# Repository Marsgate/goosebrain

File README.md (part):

# goosebrain rev 2: brain + smart pack, manual routing

This repo holds two boards that ship as one system:

- **The brain** (`kicad/thegoose.kicad_pro`): an RP2354A robot controller for six DC motors and six IO ports, with a USB-A host for a 2.4 GHz controller dongle. Its USB-C port is for programming only.
- **The smart pack** (`kicad-pack/goosepack.kicad_pro`): a small board that sits on the Ovonic 3S 450 mAh cells. It carries the charger, the protector, the 15 A fuse and its own USB-C charging port, and it plugs into the brain over an XT30 lead. Packs can be swapped, and spares can be sold.
- **The 2S smart pack** (`kicad-pack-2s/goosepack2s.kicad_pro`, started 2026-10-19): the same pack for 2-cell batteries. The charger is set for 2S by resistors, the protector is a HYCON HY2120-LB, and two HYCON HY2213 balancers replace the BQ7791501's balancing. See "The 2S pack board" below and PARTS.md. The brain runs from either pack.

The schematics are done. **The brain is placed on both sides and fully routed on 6 layers** (branch `double-sided`, 2026-10-20): 0 DRC errors, 0 unconnected items, ERC clean. See "The brain board" below and [ROUTING_LOG.md](ROUTING_LOG.md). The 3S pack board is placed and routed on 4 layers (2026-10-27, see "The pack board"); the 2S pack board is still unplaced and unrouted.

It was developed in a separate repo (goosebrain-manual), copied on 2026-10-19 from branch `rev2-rp2350` (commit `0ed7122` plus the uncommitted changes at the time) and split into brain + pack the same day. On 2026-10-20 that work, with its full history, was merged back into [Marsgate/goosebrain](https://github.com/Marsgate/goosebrain) `main`. The old SKiDL circuit generator (`circuit/`) was retired then: the KiCad schematics are the source of truth.

## The system

- **Charging:** plug the pack's USB-C into any 5 V USB charger. The pack is a plain 5 V sink (5.1 kΩ Rd on CC1/CC2, no PD), so VBUS stays at 5 V.
  - The BQ25798 runs standalone, from its power-on defaults: 3S (12.6 V), termination on, 12 h safety timer, JEITA temperature window, ADC off. No firmware can change it.
  - The ILIM_HIZ divider (39k / 24k from REGN) caps the input at about **1.04 A** (0.94–1.13 A over REGN tolerance). That gives about 0.44 A into the cells at 3.5 V/cell (1C) and 0.38 A at 4.1 V/cell, so a full charge takes about **1.2–1.3 h**.
  - A PC's USB-A port (BC1.2 SDP) is limited to 0.5 A, so charging from one takes about twice as long.
  - **The green LED on the pack** is lit while charging, off when full, and blinks on a fault.
  - **There is no cell thermistor** (removed 2026-10-26: the cells sit on the board's top side, with the parts, so no NTC can press on them). R79, a fixed 10 kΩ in TH2's old place, holds the charger's TS pin at the 25 °C point, so it always charges at the full rate and JEITA never kicks in. The protector's NTC (TH1, by the FETs) still trips on the board's temperature.
- **Protection:** BQ7791501 with low-side FETs and a 2 mΩ shunt. OV 4.25 V, UV 2.8 V per cell, OCD1 17.5 A (14 A worst case), OCD2 30 A, SCD 60 A, OCC 10 A, plus the 15 A fast fuse.
- **Clearing a trip:** an over-current trip clears when the load goes away. **Unplug the pack, or switch the brain off and on.** R94 (100 kΩ, PACK− to cell −) lets the protector see the load removed even with the charger's 17 µA standby draw on the pack.
- **The brain** takes the pack's XT30U-F lead on J3, a horizontal XT30PW-M whose mouth faces out through the bottom wall (pin 1 GND = PACK−, pin 2 PACK+). The power switch drives Q1. With the switch off, nothing on the brain loads the pack.
- **Programming:** the brain's USB-C powers the MCU through U8 alone, so you can flash it with no pack or with the switch off.

## Firmware changes

- **`code/` is the old firmware.** It's the ESP32 program (Bluepad32, ESP32Servo, DRV8848 pins) from before rev 2 and doesn't run on the RP2354A. Rev 2 needs a new firmware built around the pin map below and a USB host stack for the dongle (Pico-PIO-USB).
- **Core supply:** DVDD comes from an external 1.1 V LDO (U12), not the RP2354's own regulator (RP2350 datasheet §6.3.7). Early in boot, set the VREG register's HIZ bit to shut the on-chip regulator down (it starts anyway and draws about 400 µA until then). Never put it in low-power mode, which connects it straight to DVDD. The core voltage is fixed at 1.1 V, so don't raise it in software (`vreg_set_voltage`) or overclock past the default 150 MHz.
- **GPIO map (double-sided board, 2026-10-20):** the pins were reshuffled so each signal leaves U10 on the side facing where it goes. The MCU sheet's GPIO MAP note has the full list:
  - Motors (IN1/IN2, one PWM slice each): M1 GPIO26/27 (slice 5), M2 GPIO22/23 (slice 3), M3 GPIO20/21 (slice 2), M4 GPIO16/17 (slice 0), M5 GPIO12/13 (slice 6), M6 GPIO14/15 (slice 7).
  - LED stick data: GPIO29.
  - USB-A host: GPIO25 = D+, GPIO24 = D−. D− is the lower pin, so configure Pico-PIO-USB with `pin_dp = 25` and `pinout = PIO_USB_PINOUT_DMDP`.
  - Battery sense: GPIO28 (ADC2), unchanged.
- **Spare GPIOs:** GPIO4–7, GPIO10, GPIO11, GPIO18 and GPIO19 are no-connects.
- **IO ports:** IO1–IO6 are GPIO0, 1, 2, 3, 8 and 9. All six are 5 V tolerant, because none is on an ADC pin (GPIO26–29). IO4–IO6 can run servos from hardware PWM (slices 1B, 4A and 4B; IO5 and IO6 share slice 4, so they share a frequency), and no motor uses slice 1 or 4. IO1 and IO2 share slice 0 with M4, and IO3 shares slice 1 with IO4, so drive their servos from PIO.
- **No I2C charger:** drop the charger driver. The battery voltage now comes only from the GPIO28 divider (VSYS / 4.7, so 12.6 V reads 2.68 V). It reads 0 with the switch off.
- **The pack cuts off in hardware:** the 3S pack at 2.8 V per cell (8.4 V), the 2S pack at 2.8 V per cell (5.6 V; the HY2120 turns back on at 3.0 V per cell). Warn the user well above that, at about 3.3 V per cell.
- **Work out the cell count at power-on** from the GPIO28 reading: above about 8.6 V it's a 3S pack, otherwise 2S. The only pack this reads wrong is a nearly flat 3S one, and the cutoff is in hardware, so the cost is only a wrong warning level.
- **Motor speed:** the motors run about 40 % slower on a 2S pack. To make the robot behave the same on either pack, cap the 3S PWM to match.
- **Motors:** six DRV8251As, one per motor, on the GPIO pairs above (IN1 = GPIOn_MxA, IN2 = GPIOn_MxB). M2, M4 and M6 stay wired reversed. There is no DRV_SLEEP or DRV_FAULT: a driver sleeps when both inputs stay low for about 1 ms. Each driver limits itself at about 1.36 A (shared VREF 2.53 V, 1.2 kΩ on IPROPI, so 1.34 A). They run from 4.5 V, so a 2S pack works.
- **USB-A:** the port is always powered through a 0.5 A PTC. There is no USBA_VBUS_EN. R109/R114 (15 kΩ) are the host pull-downs on D+/D−, so Pico-PIO-USB doesn't need the GPIO pull-downs on GPIO24/25.
- **Start the USB host only when VSYS is present** (GPIO28 reads a pack). U11's VP is on VCC, which is 0 V on USB-C power alone; driving GPIO24/25 high then back-powers VCC (the dongle, J5's servos, the LED stick) at about 2.5 V through R48/R49 and U11's diodes.
- **Motor PWM:** a DRV8251A sleeps after 0.8–1.5 ms with both inputs low and takes 250 µs to wake, so use drive/brake (slow-decay) PWM, or coast PWM above a few kHz, so the off time never reaches that.
- **Entering BOOTSEL:** there's no RUN button, and with the pack on, +3V3 stays up through D3, so unplugging USB-C doesn't reset the chip. Switch off, hold BOOT (SW2) and plug in USB-C; or hold BOOT and short TP3 (RUN) to TP4 (GND); or reboot into BOOTSEL from firmware with picotool.
- **RP2350 erratum E9:** it affects only the A2 stepping, and R109/R114 (15 kΩ) are above its 8.2 kΩ limit. Read the stepping of the first boards (`picotool info`); on A2, a USB-A unplug may not be detected.

## Bring-up tests

1. **Pack charge current:** with a USB-C charger, measure the cell current at about 3.5 V/cell (expect about 0.42–0.44 A) and at 4.1 V/cell (about 0.36–0.38 A). Also try a C-to-C cable from a PD-only charger: the datasheet doesn't say what the BQ25798's D+/D− detection reports for a source with open D+/D−. If it reports SDP, charging is limited to 0.5 A in.
2. **Trip recovery:** short the pack output through a 10 A-rated load to trip OCD, then check that unplugging the pack clears it. Trip it again with the brain connected and check that the brain's power switch clears it.
3. **TS:** with USB-C in, check that TS (U7 pin 16) sits at about 59 % of REGN, inside the 10–45 °C band, and that charging runs at the full rate.
4. **Motors:** stall one motor and check the current chops at about 1.36 A.
5. **2S pack:** check that the charge stops at 8.4 V, measure the charge current (about 0.42 A at 3.5 V/cell), and check that each HY2213 bleeds about 89 mA once its cell passes 4.20 V. Trip the HY2120 with a load: over-current near 18–20 A, depending on how hot Q2/Q3 are. Then check that unplugging clears it.
6. **Brain on 2S:** at 5.6 V in (the 2S cutoff), check that Q1 is fully on (about −5 V gate drive), that VCC holds 4.96 V with the servos loaded, and that the soft start still takes about 70 µs with C71 at 10 nF.
7. **Core supply (+1V1):** measure +1V1 at C86 at idle, then with the CPU at its highest clock and the USB host running. It should stay at 1.1 V (U12's tolerance is ±1.4 %). Check that the firmware sets the VREG register's HIZ bit after boot: +3V3 current drops by about 0.4 mA when it does.
8. **Buck load step:** step the VCC load (servos) and watch VCC. If it rings, change C16 to 2.7 nF and add 39 pF from COMP (U4 pin 6) to GND, as DS41979 Table 1 does (there's no pad for it, so tack it onto C16's GND end). With L1 at 2.2 µH the ripple at 12.6 V in is about 2.7 A p-p, so expect about 4.5 A of usable output, not 5 A.
9. **Q1 turn-off:** switch off with a motor stalled and scope Q1's gate and VSYS. R40 (47k) with C71 + C72 takes about 5 ms to turn it off, so it passes through its linear region while the motors draw current.
10. **Shared motor VREF:** during test 4, also stall several motors at once and check that MOT_VREF stays at 2.53 V.

## Opening it

Open `kicad/thegoose.kicad_pro` or `kicad-pack/goosepack.kicad_pro` in KiCad 10. Both projects share the libraries in `kicad/`:

- `hexy.pretty`: the custom footprints.
- `hexyhustle.kicad_sym`: the custom symbols.
- `3dmodels`: the custom 3D models.

The pack's library tables point at `${KIPRJMOD}/../kicad/`.

## The brain board

- **Board:** 68.2 × 32 mm with 1 mm corner radii, **6 layers**, 1.6 mm thick, no mounting holes, **parts on both sides**.
  - It was 73.5 × 43.1 mm (3,169 mm²) before the double-sided build. Now it's 2,182 mm²: 31 % smaller, 5.3 mm shorter and 11.1 mm narrower.
  - It was 88.5 × 47 mm until 2026-10-19.
- **Parts:** the part numbers and the reasons behind them are in [PARTS.md](PARTS.md).
- **How it was built:** the placement, the routing passes, the 4-to-6-layer decision and the trade-offs are in [ROUTING_LOG.md](ROUTING_LOG.md). The copper is generated by scripts:
  - `tools/place_double.py` places every part.
  - `python3 tools/route_all.py` rebuilds all the copper from that placement in about 10 minutes: the scripted critical routing (`tools/route_recipe.py`), a small grid router for the rest (`tools/grid_router.py`), GND channels and stitching, and the silkscreen.
  - Hand edits to tracks are lost on the next rebuild, so change the scripts instead.

### Stackup: JLC06161H-3313

| Layer | Use | Thickness |
|---|---|---|
| F.Cu | parts, USB pairs, short signals, GND pour | 35 µm (1 oz) |
| prepreg 3313 | εr 4.1 | 0.0994 mm |
| In1.Cu | **solid GND** | 15 µm |
| core | | 0.55 mm |
| In2.Cu | signals, GND fill | 15 µm |
| prepreg 2116 | | 0.1088 mm |
| In3.Cu | GND with the VSYS, VCC and +3V3 areas; GND channels under every In2 signal | 15 µm |
| core | | 0.55 mm |
| In4.Cu | **solid GND** | 15 µm |
| prepreg 3313 | εr 4.1 | 0.0994 mm |
| B.Cu | back-side parts, signals, GND pour | 35 µm (1 oz) |

JLC quotes 1.54 mm finished.

The 4-layer stack (JLC04161H-7628) was tried first. It still left 27–60 connections unrouted after three placement passes, scripted critical routing and 30-minute Freerouting runs, and B.Cu signals would have crossed In2's power areas. Filled vias in pads are free on 6 layers. Impedance control was too when the move was made, but it cost $33.08 in the quote of 2026-10-20 (see "Ordering boards").

### What's on the board now

- **Top wall, left to right:** J1 (USB-C), J12 (LED stick, vertical PH) and J4 (USB-A). J1's and J4's plug centres are 19.5 mm apart, so an 8BitDo dongle (24 mm wide) fits next to a USB-C plug.
- **Left wall:** J5 (the 3 × 6 right-angle IO header) at the top, then M5 and M6.
- **Right wall:** M1–M4.
- **Bottom wall:** J3 (horizontal XT30) with its mouth out through the wall, SW1's lever, and SW2 (BOOT) in the bottom-right corner.
- **Front:**
  - U10 (RP2354A, at 0°) under J1, with Y1 next to it.
  - U10's core supply north-east of it: an external 1.1 V LDO (U12, TLV74311) as in the RP2350 datasheet's Fig. 24, with C86 (output) and C87 (input) beside it, so the on-chip switching regulator and its inductor aren't used. C85 (VREG_VIN) sits right off pins 47–49; VREG_FB goes to a GND via inside the pin ring and VREG_LX is open. C52, the second 4.7 µF, is on the back at DVDD pin 23.
  - The buck (U4, L1, C73/C74, C14) below U10.
  - U3/U17 beside M5/M6, and U1/U15/U2/U16 beside M1–M4.
  - Q1 east of J3.
- **Back** (all assembled by JLC except D4, U14 and F2), each part under or next to what it serves:
  - U10's decoupling, each cap on its supply via, and C52 (the second +1V1 4.7 µF) at DVDD pin 23
  - U6 (USB-C ESD) and R99/R100 under J1
  - U11, R109/R114, F2 and C59 under J4
  - U14 and C69 under J12
  - the 3.3 V LDO cluster (U8, U9, D2, C37–C40) under J3
  - the buck's output caps and feedback parts under L1
  - R55–R60 beside J5
  - the drivers' VM caps and IPROPI resistors
  - D4 and the Q1 gate network
  - TP1–TP4
  - The tallest back parts are the 1206 caps C5/C8/C12, at 1.6 mm.
- **Fiducials:** FID1–FID3 on the front and FID4–FID6 on the back. The goose logo is on the back silkscreen, wherever tools/silk.py finds room.
- **Routing:** complete.
  - `kicad-cli pcb drc --schematic-parity --severity-error` with zones refilled: 0 errors, 0 unconnected, 0 parity issues.
  - ERC: 0 violations.
  - The only DRC warnings are 9 footprints that differ from their library copies (M1–M6, J3, J4 and the logo). Their silk was trimmed at the outline, and the logo was scaled to fit.
  - 27 references are hidden: FID1–6, the caps under U10 (C52 among them), C85 by the core supply pins and a few others with no clear 0.8 mm spot. They're still on the fab layers.
- **Vias:** 0.45/0.3 mm for signals (168) and 0.6/0.3 mm for power (51), so the smallest hole on the board is 0.3 mm (the drivers' thermal vias are 0.33 mm). The signal vias were 0.45/0.25 mm until 2026-10-20; at 0.3 mm the order avoids JLC's small-via surcharge, and the annular ring is 0.075 mm. Several sit in pads, so order filled and capped vias (POFV), which are free on 6 layers.
- **"USB fan-out" rule areas:** they only exempt the short fan-out segments where a pair has to split from the diff-pair gap check.
- **"VREG corner" rule area:** over pins 47–50 and C85. The VREG_PGND, VREG_VIN and VREG_FB stubs are only as wide as the 0.2 mm pads, so inside it 0.15 mm spacing applies and the GND stubs are exempt from the 0.4 mm GND width.

## Routing rules

The net classes are set in the project file, and the custom DRC rules are in `kicad/thegoose.kicad_dru`.

| Class | Nets | Track | Clearance | Via (dia / drill) |
|---|---|---|---|---|
| Default | signals | 0.15 mm | 0.15 mm | 0.45 / 0.3 mm |
| Pack | PACK+, VSYS | 1.0 mm min | 0.2 mm | 0.8 / 0.4 mm |
| 5V | VCC, USB-A VBUS | 0.5 mm min | 0.2 mm | 0.6 / 0.3 mm |
| GND | GND | 0.4 mm min | 0.2 mm | 0.6 / 0.3 mm |
| Motor | U*_OUT1/2 | 0.4 mm min | 0.2 mm | 0.6 / 0.3 mm |
| Rail | +3V3, +1V1, VBUS | 0.2 mm | 0.2 mm | 0.45 / 0.3 mm |
| USB | USB pairs | 0.124 mm, 0.127 mm gap | 0.12 mm (0.2 mm to other nets) | 0.45 / 0.3 mm |

- **USB pairs:**
  - Route them as differential pairs: **0.124 mm tracks with a 0.127 mm gap**.
  - JLC's impedance calculator gives 90 Ω for that on F.Cu over In1 on JLC06161H-3313 (checked 2026-10-20). **Order with the stackup specified (JLC06161H-3313), not impedance control:** the stackup alone fixes the dielectric this geometry was sized for. Impedance control costs $33.08 on this order and needs an impedance spec sheet in the Gerber zip, and USB here runs at full speed (12 Mbit/s), where the pair's impedance barely matters.
  - The pairs run on F.Cu over solid In1, except J1's flipped contacts, which join on the back over solid In4.
- **Power widths:** the minimums in the table are DRC rules. Pours on those nets don't have to meet them.
- **Pack path:** PACK+ from J3 through Q1 to VSYS carries all the motor current, with stall peaks of several amps. It runs in pours on F.Cu and B.Cu and in the In3 VSYS area, with several vias at every layer change.
- **Switch node:** signals keep 0.2 mm from the buck switch node (U4 SW).
- **In2 signals** reference In3. `tools/plane_channels.py` cuts a GND channel (track + 0.5 mm each side) out of the In3 power areas under every In2 signal.
- **Board edge:** copper keeps 0.3 mm from the edge, JLC's limit for routed edges.

## The pack board

`kicad-pack/goosepack.kicad_pcb` is **placed and routed** (2026-10-27, charger reworked the same day): **50 × 23 mm**, the smallest board with every part on the top side (so JLC's Economic PCBA, top side only, still works) and every capacitor and resistor within 9 mm of the pin it serves (the TS, ILIM_HIZ and PROG dividers, which only set DC levels, and C34 sit further out). The parts also pack onto 45.5 × 20.5 mm, but only with the charger's last passives 13–22 mm from their pins, and that board didn't route. It uses the 4-layer JLC04161H-7628 stackup (the brain moved to 6 layers). DRC with zones refilled: 0 errors, 0 unconnected items, two warnings (J11's silk was trimmed at the board edge and U7's pin 1 mark nudged off C22, so neither matches its library footprint); schematic parity and ERC are clean. The housing is designed around this outline.

`tools/place_pack.py compact` rebuilds the placement (run with KiCad's Python; `--size` and `--reach` try other sizes and reach limits, `--led=stat` puts LED1 by U7 instead of the edge). Then `tools/route_pack.py setup`, `route` and `finish` rebuild the copper, and `tools/silk.py pack` places the references and the polarity labels (see each docstring). Routing takes about 10 minutes; every step takes `--pcb=FILE` to work on a copy, and `route --order=NET,...` tries another route order. Its other layouts (`vertical`, `rightangle`, `ontop`) were the earlier options for a board sized to the Ovonic pack; renders of all of them are in `renders/pack/`.

The whole process, from placement to the JLC order, with what went wrong along the way, is in [docs/3s-pack-process.md](docs/3s-pack-process.md). Follow it for the 2S pack.

- **Top:** power row along the bottom edge (J3 pads, F1 over R66, Q2/Q3 back to back, J2 pads), J11 and U13 above it, the charger and J1 at the east end, LED1 on the east edge above J1. J1's face sticks out about 1.4 mm past the east edge.
- **The charger's power stage** follows TI's BQ25798 layout example (SLUSDV2C §8.4.2): U7's power pins face west into L2, the SYS caps (C32, C27–C30) sit in a row north of L2 and the PMID caps (C26, C24, C25) in a row south of it, each row on an F.Cu pour from its pin with its 100 nF cap nearest, and PGND runs out between L2's pads to five vias under L2's body. The boot caps are 0402: C18 under L2 with its SW1 pad on the SW1 pour (BTST1 about 6.4 mm, partly on B.Cu), C19 over pin 19 (BTST2 1.5 mm; SW2 back by a via and about 7 mm of 0.4 mm In2). The REGN, VBUS and BAT caps sit at their pins.
- **Polarity:** B−/B+ by J3's pads (the cells), P−/P+ by J2's (the output; the square pads are negative), and B0–B3 under J11's pins.
- **Heights above the board:** J11 7.0 mm (about 12 mm with the balance plug in), J1 3.3 mm, L2 3.0 mm, F1 2.7 mm, D1 2.4 mm, the rest under 1.8 mm.
- **Back:** no parts, only the clipped leads of J2, J3 and J11 (keep them to 1.5 mm).
- **Pigtails:** J3 takes a 16 AWG lead ending in an XT30U-M that the pack's own XT30U-F plugs into, so the cell leads stay uncut. J2 takes the 16 AWG output lead with the XT30U-F that mates the brain's J3. Both use KiCad's `SolderWire-1.5sqmm_1x02_P6mm` pads. J11 stays a B4B-XH-A header: JST XH has no wire-to-wire male, so the balance lead can't become a pigtail.
- There are no mounting holes: the housing holds the board by its edges.
- The housing shows LED1 and the USB-C opening.
- R66 is a TA-I RLP25 2 mΩ 2512 metal shunt. It uses KiCad's generic 2512 land pattern for now: check TA-I's recommended pads before ordering.

Routing:

- **Layers:** F.Cu carries the parts, signals and the pack-path pours (J3 → F1 → PACK+, BAT_N → R66 → Q2 → Q3 → PACK- → J2). In1 is ground, split between BAT_N (the cells' negative, under the protector) and PACK- (the charger's and the brain's ground). In2 carries PACK+ in a band from F1 to J2 and is otherwise a signal layer. B.Cu carries signals. F.Cu, In2 and B.Cu are filled with the same ground split, stitched to In1 every 2.5 mm where both fills reach.
- **Widths:** the pack path and the charger's power stage are pours. Power and plane-net tracks are 0.4 mm. The charger's routed power nets (VBUS, PMID, SYS) are 0.3 mm, since the BQ25798's 0.2 mm pads at 0.4–0.46 mm pitch take nothing wider at 0.2 mm clearance; `finish` widens them to 0.4 mm wherever DRC still passes (VBUS and PACK+ to 0.6 or 0.5 mm on In2 first). VBUS still has about 12 mm of 0.3 mm on In2, which carries only C21's and D1's branches, not the input current. Signals are 0.15 mm.
- **Vias:** 0.45/0.3 mm for signals (as on the brain), 0.5/0.3 or 0.6/0.3 mm for the power classes (the router picks by net class), none within 0.2 mm of an SMD pad. The vias under U7's body (no exposed pad) are its east-side and corner escapes: SDA, SCL, SDRV, the east ground pins; VBUS's east pins join pins 2 and 3 by an F.Cu strip under the body instead.
- **Current sense:** Kelvin lines on B.Cu from vias at the inner edges of R66's pads to R68 and R69 (the SRP/SRN filter, with C68 across U13's pins). Rule areas keep the fills off the BAT_N line and its vias, so it meets BAT_N only at R66's pad.
- **Router:** `tools/grid_router.py --board=pack`, the brain's router. Freerouting 2.1 stalled at 25–40 unrouted connections and ignores its pass limits. `route_pack.py setup` lays the connections that no route order could fit around U7 (escape vias for its crowded corners and J1's CC2 and north VBUS pads, C18's and C19's boot loops, a stub out of C36's SDRV pad), and keeps ILIM_HIZ 1 mm off SW2's In2 run with a router-only keepout; `route` then routes STAT, CHG_SYS, BTST1 and PROG first and the rest in the router's own order. `tools/route_loop.py` wraps the router in a diagnose-and-retry loop for an LLM (or a person) to drive: each attempt routes a copy with `tools/route_llm.py` (grid_router plus a diagnosis of each failed pair; `tools/escape.py` adds pin escapes) and writes the failures, the nets in the way and a hint to a JSON report. That loop found the route orders above.

Open layout items (fresh-eyes reviews on 2026-10-27 scored the board 2.4, then 3.4 and 3.5 of 5 after the charger rework; the last found no blockers). Decided the same day: D1 is an SMBJ15A (24.4 V clamp, under the BQ25798's 30 V VBUS maximum; see PARTS.md) and the finish is lead-free HASL (ENIG would add $16.70 for 5 boards; OSP ages before the hand-soldered parts go on).

- **The boot loops** are the shortest this footprint allows with every part on top: TI's example runs SW1/SW2 through vias inside U7's pads, which single-sided assembly without via-in-pad can't do. BTST1 is about 6.4 mm with two vias, and C19's SW2 return about 7.7 mm through In2.
- **C36** (SDRV's 1 nF) sits about 9 mm from its pin's via; nothing closer is free, and SDRV is a static charge-pump output.
- **Q2 and Q3** only have the F.Cu drain pour for heat (about 1 W each at 15 A).
- **References:** 44 are hidden for lack of room (no reference may sit over another part); the fab layers keep them all.
- **R66** uses KiCad's generic 2512 land pattern: check TA-I's recommended pads (see above).

## The 2S pack board

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
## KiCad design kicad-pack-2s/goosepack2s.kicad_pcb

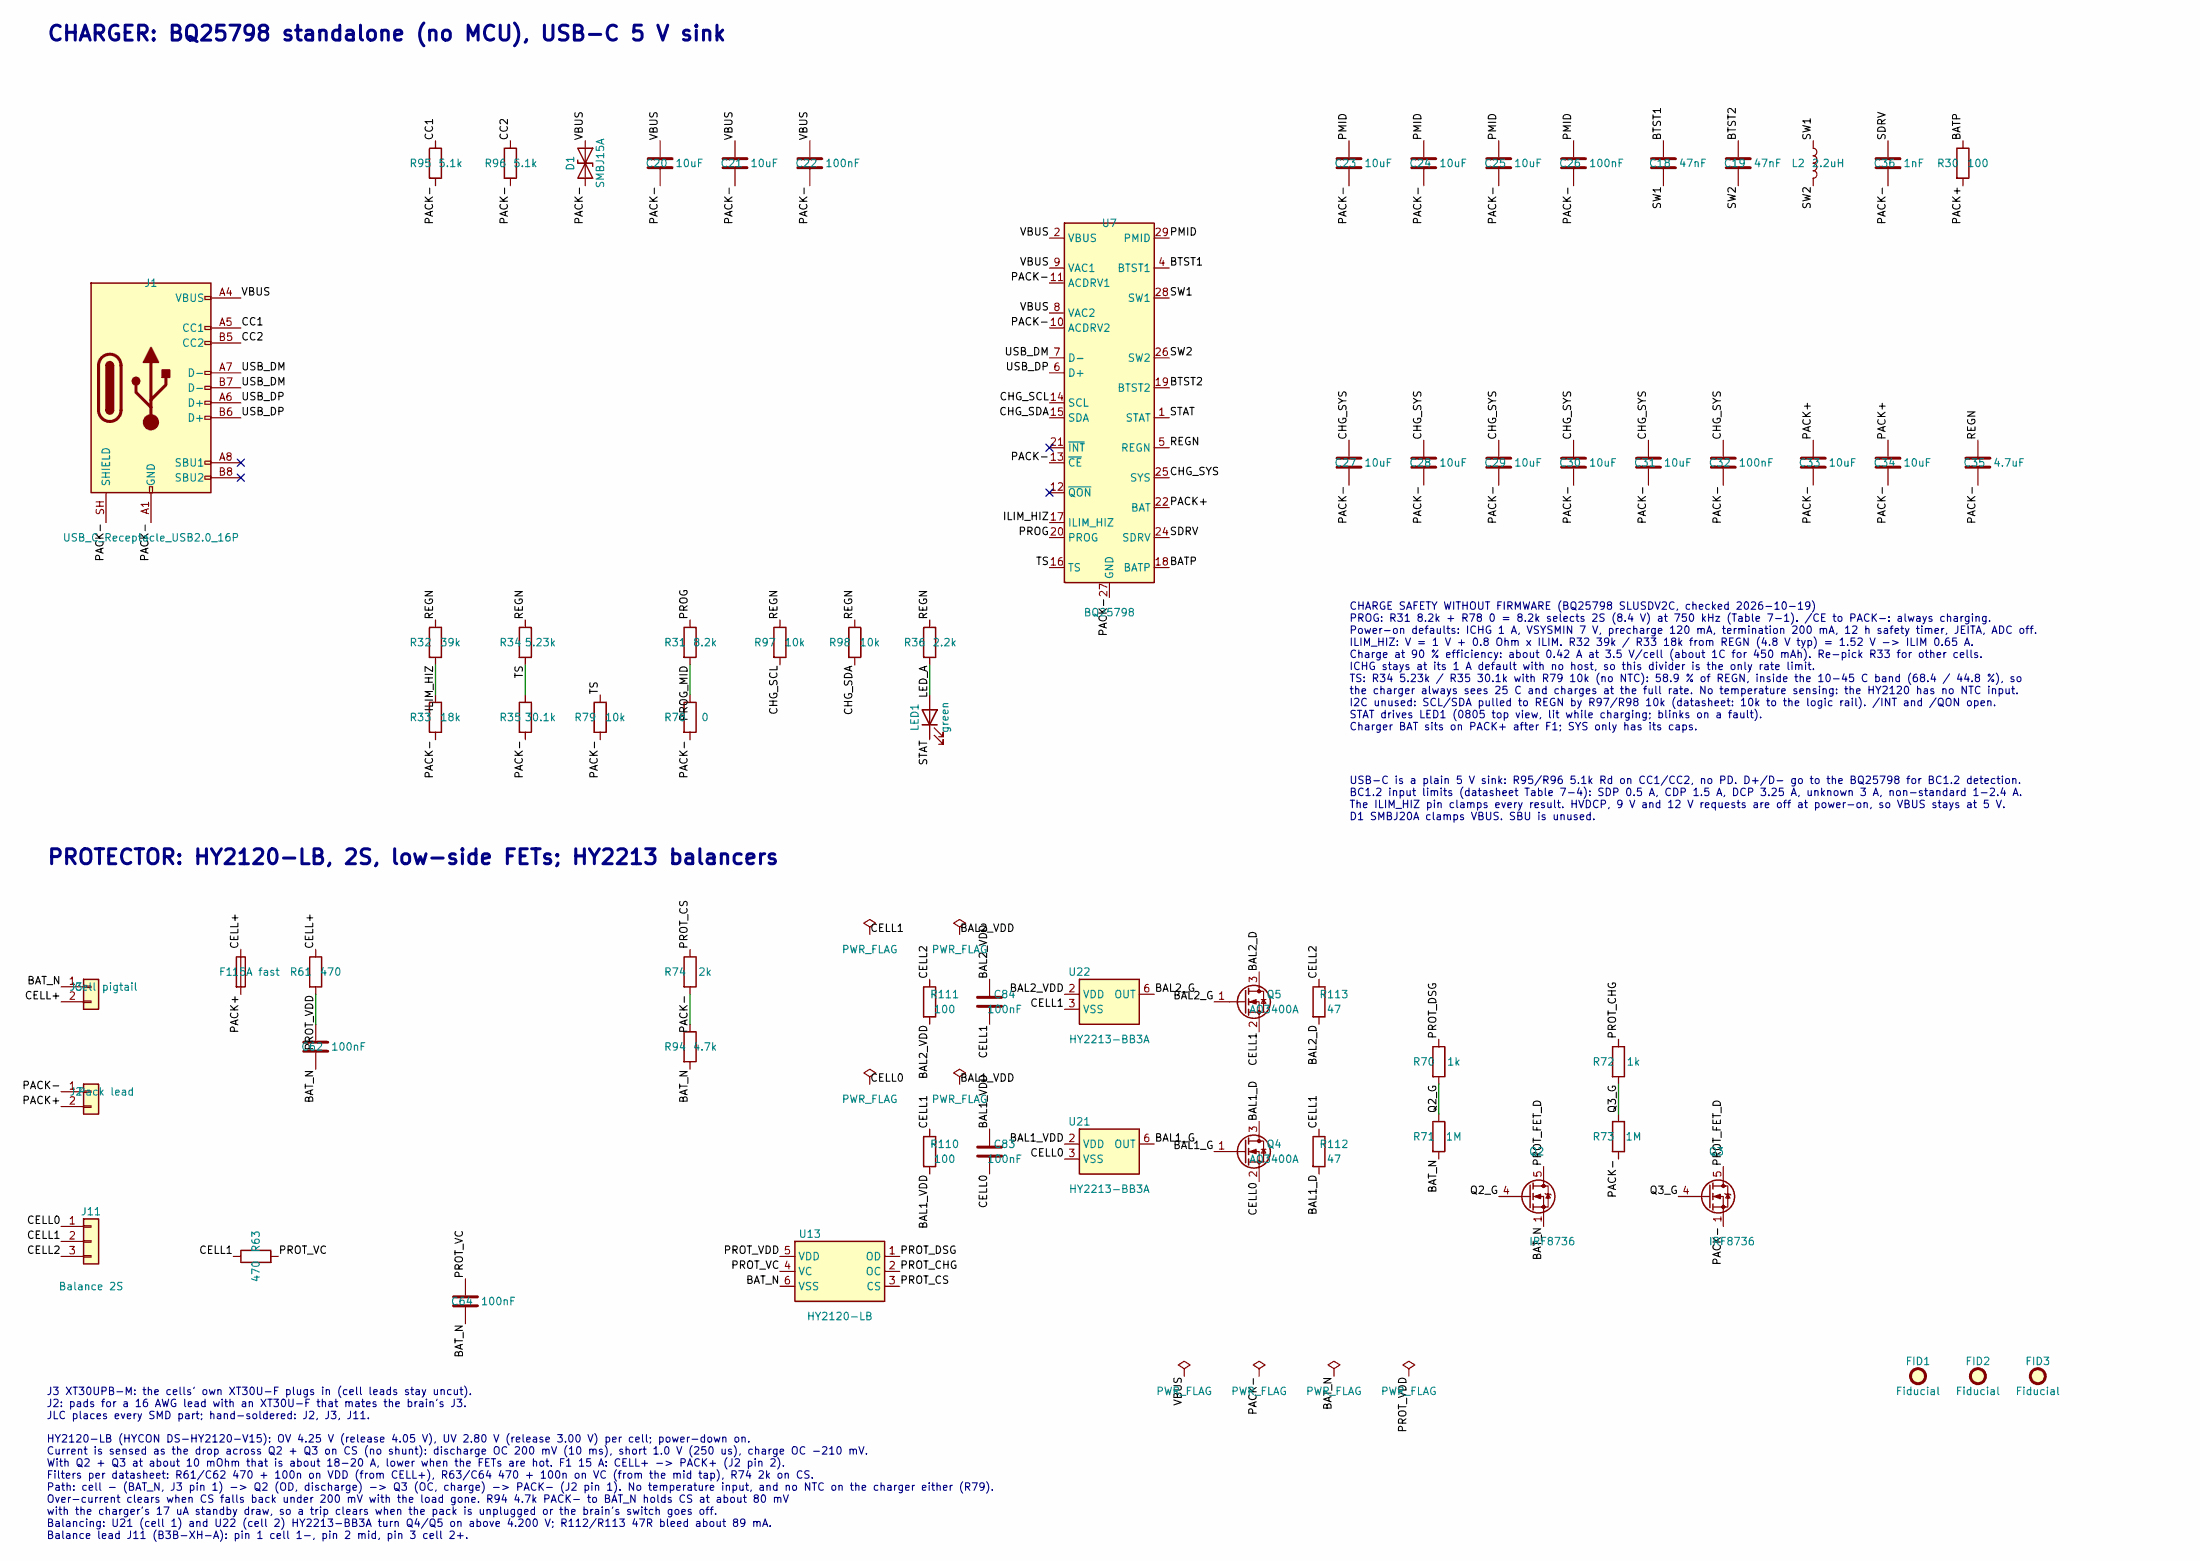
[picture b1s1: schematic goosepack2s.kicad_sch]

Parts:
C18, C19: 47nF; C_0402_1005Metric; MPN 0402B473K160NT; LCSC Part # C192385
C20, C21, C23, C24, C25, C27, C28, C29, C30, C31, C33, C34: 10uF; C_0805_2012Metric; MPN CL21A106KAYNNNE; LCSC Part # C15850
C22, C26, C32, C62, C64, C83, C84: 100nF; C_0402_1005Metric; MPN CL05B104KO5NNNC; LCSC Part # C1525
C35: 4.7uF; C_0603_1608Metric; MPN CL10A475KO8NNNC; LCSC Part # C19666
C36: 1nF; C_0402_1005Metric; MPN 0402B102K500NT; LCSC Part # C1523
D1: SMBJ15A; D_SMB; MPN SMBJ15A; LCSC Part # C19077569
F1: 15A fast; Fuse_Littelfuse-NANO2-451_453; MPN 0453015.MR; LCSC Part # C178997
FID1, FID2, FID3: Fiducial; Fiducial_1mm_Mask2mm
J1: USB_C_Receptacle_USB2.0_16P; USB_C_Receptacle_ShouHan_TYPE-C16PIN; MPN TYPE-C16PIN; LCSC Part # C393939
J2: Pack lead; SolderWire-1.5sqmm_1x02_P6mm_D1.7mm_OD3mm; MPN XT30U-F; LCSC Part # C99102
J3: Cell pigtail; SolderWire-1.5sqmm_1x02_P6mm_D1.7mm_OD3mm; MPN XT30U-M; LCSC Part # C99101
J11: Balance 2S; JST_XH_B3B-XH-A_1x03_P2.50mm_Vertical; MPN B3B-XH-A(LF)(SN); LCSC Part # C144394
L2: 2.2uH; L_Changjiang_FNR4030S; MPN FNR4030S2R2MT; LCSC Part # C167869
LED1: green; LED_0805_2012Metric; MPN KT-0805G; LCSC Part # C2297
Q2, Q3: IRF8736; SOIC-8_3.9x4.9mm_P1.27mm; MPN IRF8736TRPBF; LCSC Part # C51630
Q4, Q5: AO3400A; SOT-23-3; MPN AO3400A; LCSC Part # C20917
R30, R110, R111: 100; R_0402_1005Metric; MPN 0402WGF1000TCE; LCSC Part # C25076
R31: 8.2k; R_0402_1005Metric; MPN 0402WGF8201TCE; LCSC Part # C25924
R32: 39k; R_0402_1005Metric; MPN 0402WGF3902TCE; LCSC Part # C25783
R33: 18k; R_0402_1005Metric; MPN 0402WGF1802TCE; LCSC Part # C25762
R34: 5.23k; R_0402_1005Metric; MPN RTT025231FTH; LCSC Part # C11631
R35: 30.1k; R_0402_1005Metric; MPN 0402WGF3012TCE; LCSC Part # C29402
R36: 2.2k; R_0402_1005Metric; MPN 0402WGF2201TCE; LCSC Part # C25879
R61, R63: 470; R_0402_1005Metric; MPN 0402WGF4700TCE; LCSC Part # C25117
R70, R72: 1k; R_0402_1005Metric; MPN 0402WGF1001TCE; LCSC Part # C11702
R71, R73: 1M; R_0402_1005Metric; MPN 0402WGF1004TCE; LCSC Part # C26083
R74: 2k; R_0402_1005Metric; MPN 0402WGF2001TCE; LCSC Part # C4109
R78: 0; R_0402_1005Metric; MPN 0402WGF0000TCE; LCSC Part # C17168
R79: 10k; R_0603_1608Metric; MPN 0603WAF1002T5E; LCSC Part # C25804
R94: 4.7k; R_0402_1005Metric; MPN 0402WGF4701TCE; LCSC Part # C25900
R95, R96: 5.1k; R_0402_1005Metric; MPN 0402WGF5101TCE; LCSC Part # C25905
R97, R98: 10k; R_0402_1005Metric; MPN 0402WGF1002TCE; LCSC Part # C25744
R112, R113: 47; R_2512_6332Metric; MPN 25121WJ0470T4E; LCSC Part # C15261
U7: BQ25798; Texas_RQM0029A_VQFN-29_4x4mm_P0.4mm; MPN BQ25798RQMR; LCSC Part # C2876593
U13: HY2120-LB; SOT-23-6; MPN HY2120-LB; LCSC Part # C168778
U21, U22: HY2213-BB3A; SOT-23-6; MPN HY2213-BB3A; LCSC Part # C113632

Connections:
/BAL1_D: Q4.3 (D), R112.2
/BAL1_G: Q4.1 (G), U21.6 (OUT)
/BAL1_VDD: C83.1, R110.2, U21.2 (VDD)
/BAL2_D: Q5.3 (D), R113.2
/BAL2_G: Q5.1 (G), U22.6 (OUT)
/BAL2_VDD: C84.1, R111.2, U22.2 (VDD)
/BATP: R30.1, U7.18 (BATP)
/BAT_N: C62.2, C64.2, J3.1, Q2.1 (S), Q2.2 (S), Q2.3 (S), R71.2, R94.2, U13.6 (VSS)
/BTST1: C18.1, U7.4 (BTST1)
/BTST2: C19.1, U7.19 (BTST2)
/CC1: J1.A5 (CC1), R95.1
/CC2: J1.B5 (CC2), R96.1
/CELL0: C83.2, J11.1, Q4.2 (S), U21.3 (VSS)
/CELL1: C84.2, J11.2, Q5.2 (S), R63.1, R110.1, R112.1, U22.3 (VSS)
/CELL2: J11.3, R111.1, R113.1
/CELL+: F1.1, J3.2, R61.1
/CHG_SCL: R97.2, U7.14 (SCL)
/CHG_SDA: R98.2, U7.15 (SDA)
/CHG_SYS: C27.1, C28.1, C29.1, C30.1, C31.1, C32.1, U7.25 (SYS)
/ILIM_HIZ: R32.2, R33.1, U7.17 (ILIM_HIZ)
/LED_A: LED1.2 (A), R36.2
/PACK+: C33.1, C34.1, F1.2, J2.2, R30.2, U7.22 (BAT), U7.23 (BAT)
/PACK-: C20.2, C21.2, C22.2, C23.2, C24.2, C25.2, C26.2, C27.2, C28.2, C29.2, C30.2, C31.2, C32.2, C33.2, C34.2, C35.2, C36.2, D1.2 (A2), J1.A1 (GND), J1.A12 (GND), J1.B1 (GND), J1.B12 (GND), J1.SH (SHIELD), J2.1, Q3.1 (S), Q3.2 (S), Q3.3 (S), R33.2, R35.2, R73.2, R74.2, R78.2, R79.2, R94.1, R95.2, R96.2, U7.10 (ACDRV2), U7.11 (ACDRV1), U7.13 (~CE), U7.27 (GND)
/PMID: C23.1, C24.1, C25.1, C26.1, U7.29 (PMID)
/PROG: R31.1, U7.20 (PROG)
/PROG_MID: R31.2, R78.1
/PROT_CHG: R72.1, U13.2 (OC)
/PROT_CS: R74.1, U13.3 (CS)
/PROT_DSG: R70.1, U13.1 (OD)
/PROT_FET_D: Q2.5 (D), Q2.6 (D), Q2.7 (D), Q2.8 (D), Q3.5 (D), Q3.6 (D), Q3.7 (D), Q3.8 (D)
/PROT_VC: C64.1, R63.2, U13.4 (VC)
/PROT_VDD: C62.1, R61.2, U13.5 (VDD)
/Q2_G: Q2.4 (G), R70.2, R71.1
/Q3_G: Q3.4 (G), R72.2, R73.1
/REGN: C35.1, R32.1, R34.1, R36.1, R97.1, R98.1, U7.5 (REGN)
/SDRV: C36.1, U7.24 (SDRV)
/STAT: LED1.1 (K), U7.1 (STAT)
/SW1: C18.2, L2.1, U7.28 (SW1)
/SW2: C19.2, L2.2, U7.26 (SW2)
/TS: R34.2, R35.1, R79.1, U7.16 (TS)
/USB_DM: J1.A7 (D-), J1.B7 (D-), U7.7 (D-)
/USB_DP: J1.A6 (D+), J1.B6 (D+), U7.6 (D+)
/VBUS: C20.1, C21.1, C22.1, D1.1 (A1), J1.A4 (VBUS), J1.A9 (VBUS), J1.B4 (VBUS), J1.B9 (VBUS), U7.2 (VBUS), U7.3 (VBUS), U7.8 (VAC2), U7.9 (VAC1)

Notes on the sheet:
CHARGER: BQ25798 standalone (no MCU), USB-C 5 V sink
PROTECTOR: HY2120-LB, 2S, low-side FETs; HY2213 balancers
USB-C is a plain 5 V sink: R95/R96 5.1k Rd on CC1/CC2, no PD. D+/D- go to the BQ25798 for BC1.2 detection. BC1.2 input limits (datasheet Table 7-4): SDP 0.5 A, CDP 1.5 A, DCP 3.25 A, unknown 3 A, non-standard 1-2.4 A. The ILIM_HIZ pin clamps every result. HVDCP, 9 V and 12 V requests are off at pow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
CHARGE SAFETY WITHOUT FIRMWARE (BQ25798 SLUSDV2C, checked 2026-10-19) PROG: R31 8.2k + R78 0 = 8.2k selects 2S (8.4 V) at 750 kHz (Table 7-1). /CE to PACK-: always charging. Power-on defaults: ICHG 1 A, VSYSMIN 7 V, precharge 120 mA, termination 200 mA, 12 h safety timer, JEITA, ADC off. ILIM_HIZ: 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
HY2120-LB (HYCON DS-HY2120-V15): OV 4.25 V (release 4.05 V), UV 2.80 V (release 3.00 V) per cell; power-down on. Current is sensed as the drop across Q2 + Q3 on CS (no shunt): discharge OC 200 mV (10 ms), short 1.0 V (250 us), charge OC -210 mV. With Q2 + Q3 at about 10 mOhm that is about 18-20 A, 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
J3 XT30UPB-M: the cells' own XT30U-F plugs in (cell leads stay uncut). J2: pads for a 16 AWG lead with an XT30U-F that mates the brain's J3. JLC places every SMD part; hand-soldered: J2, J3, J11.

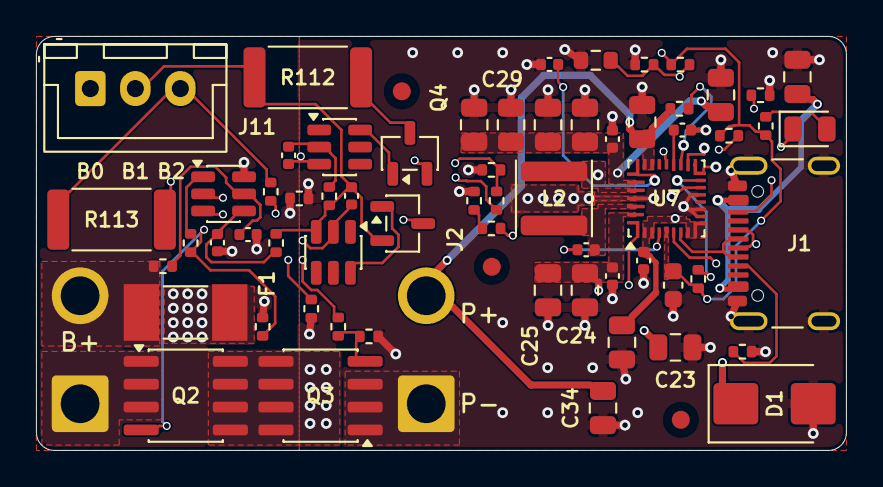
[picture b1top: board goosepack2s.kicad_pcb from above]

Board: 4 copper layers, 45.0 x 23.0 mm, 67 parts (0 on the bottom side), 43 nets.

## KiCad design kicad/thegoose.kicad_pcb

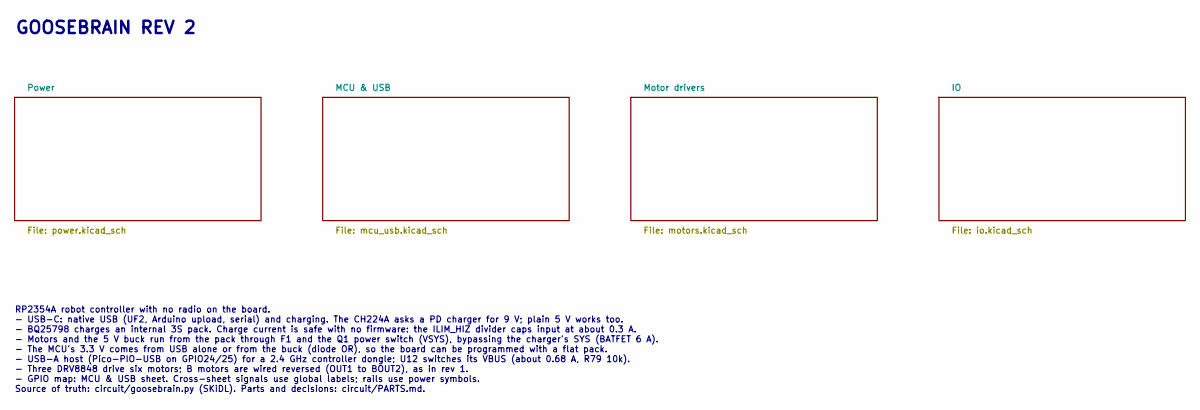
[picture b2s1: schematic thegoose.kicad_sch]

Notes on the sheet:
GOOSEBRAIN REV 2
RP2354A robot controller with no radio on the board. - USB-C: native USB (UF2, Arduino upload, serial) and charging. The CH224A asks a PD charger for 9 V; plain 5 V works too. - BQ25798 charges an internal 3S pack. Charge current is safe with no firmware: the ILIM_HIZ divider caps input at about 0.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

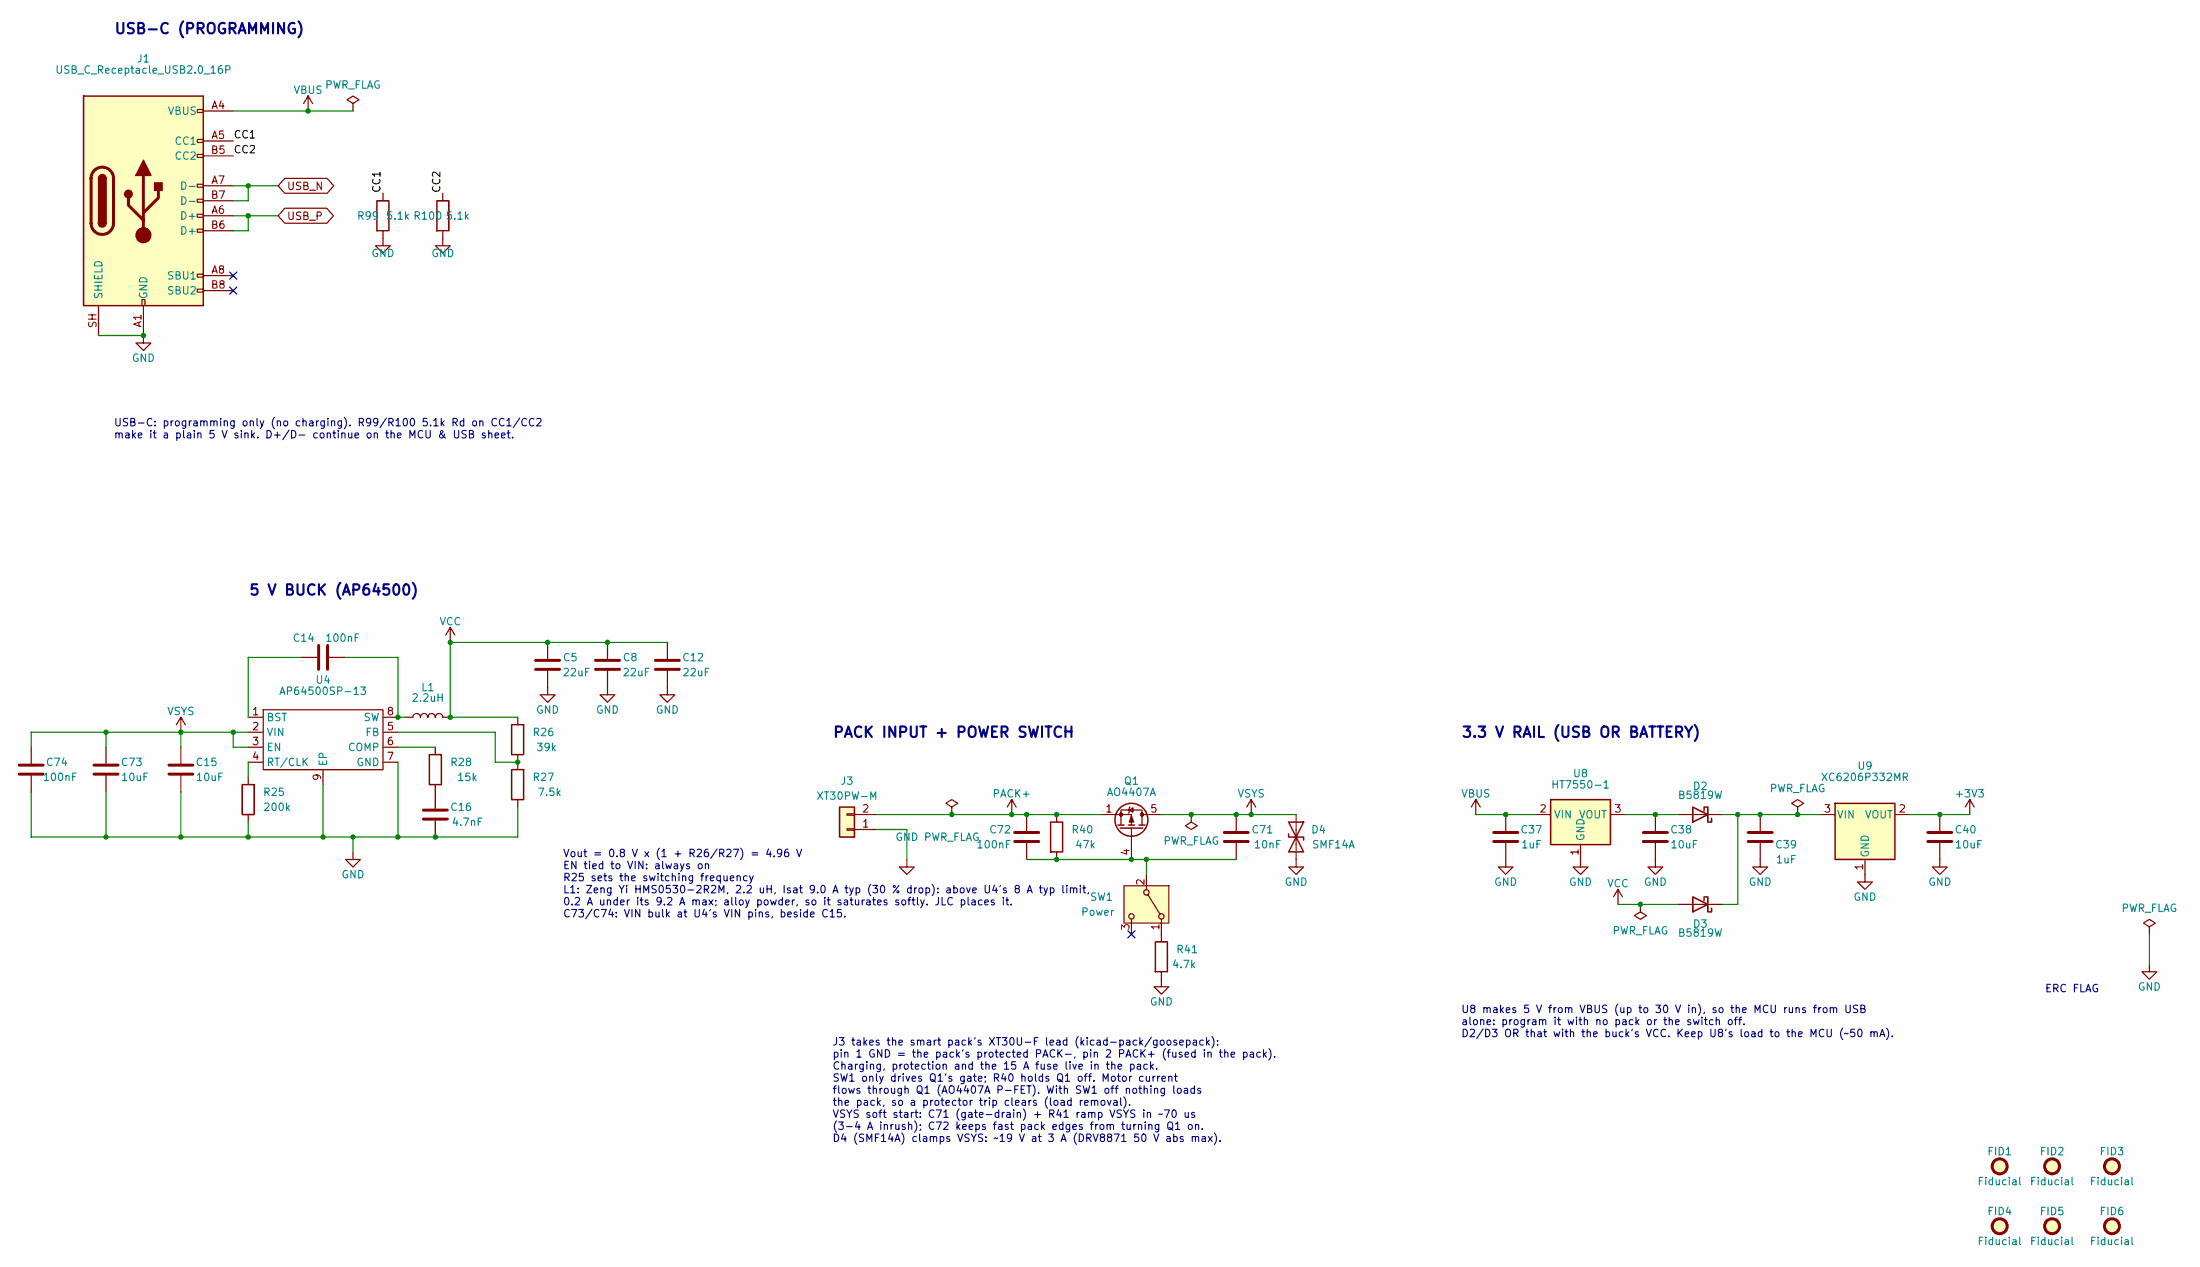
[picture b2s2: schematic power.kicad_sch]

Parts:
C5, C8, C12: 22uF; C_1206_3216Metric; MPN CL31A226KPHNNNE; LCSC Part # C5672
C14, C72: 100nF; C_0805_2012Metric; MPN CC0805KRX7R9BB104; LCSC Part # C49678
C15, C73: 10uF; C_0805_2012Metric; MPN CL21A106KAYNNNE; LCSC Part # C15850
C16: 4.7nF; C_0402_1005Metric; MPN 0402B472K500NT; LCSC Part # C1538
C37: 1uF; C_0603_1608Metric; MPN CL10A105KB8NNNC; LCSC Part # C15849
C38, C40: 10uF; C_0603_1608Metric; MPN CL10A106KP8NNNC; LCSC Part # C19702
C39: 1uF; C_0402_1005Metric; MPN CL05A105KA5NQNC; LCSC Part # C52923
C71: 10nF; C_0402_1005Metric; MPN CL05B103KB5NNNC; LCSC Part # C15195
C74: 100nF; C_0402_1005Metric; MPN CL05B104KB54PNC; LCSC Part # C307331
D2, D3: B5819W; D_SOD-123; MPN B5819W; LCSC Part # C64885
D4: SMF14A; D_SMF; MPN SMF14A; LCSC Part # C207256
FID1, FID2, FID3, FID4, FID5, FID6: Fiducial; Fiducial_1mm_Mask2mm
J1: USB_C_Receptacle_USB2.0_16P; USB_C_Receptacle_ShouHan_TYPE-C16PIN; MPN TYPE-C16PIN; LCSC Part # C393939
J3: XT30PW-M; AMASS_XT30PW-M_1x02_P2.50mm_Horizontal; MPN XT30PW-M30.G.Y; LCSC Part # C431092
L1: 2.2uH; L_ZengYi_HMS0530; MPN HMS0530-2R2M; LCSC Part # C18734448
Q1: AO4407A; SOIC-8_3.9x4.9mm_P1.27mm; MPN AO4407A; LCSC Part # C2841482
R25: 200k; R_0402_1005Metric; MPN 0402WGF2003TCE; LCSC Part # C25764
R26: 39k; R_0402_1005Metric; MPN 0402WGF3902TCE; LCSC Part # C25783
R27: 7.5k; R_0402_1005Metric; MPN 0402WGF7501TCE; LCSC Part # C25918
R28: 15k; R_0402_1005Metric; MPN 0402WGF1502TCE; LCSC Part # C25756
R40: 47k; R_0402_1005Metric; MPN 0402WGF4702TCE; LCSC Part # C25792
R41: 4.7k; R_0402_1005Metric; MPN 0402WGF4701TCE; LCSC Part # C25900
R99, R100: 5.1k; R_0402_1005Metric; MPN 0402WGF5101TCE; LCSC Part # C25905
SW1: Power; SW_SPDT_ShouHan_SK12D07VG4; MPN SK12D07VG4; LCSC Part # C393937
U4: AP64500SP-13; Diodes_SO-8EP; MPN AP64500SP-13; LCSC Part # C2070920
U8: HT7550-1; SOT-89-3; MPN HT7550-1; LCSC Part # C16106
U9: XC6206P332MR; SOT-23-3; MPN XC6206P332MR-G; LCSC Part # C5446

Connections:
+3V3: C40.1, U9.2 (VOUT); also elsewhere on the board
/Power/CC1: J1.A5 (CC1), R99.1
/Power/CC2: J1.B5 (CC2), R100.1
GND: C5.2, C8.2, C12.2, C15.1, C16.1, C37.2, C38.2, C39.2, C40.2, C73.1, C74.1, D4.2 (A2), J1.A1 (GND), J1.A12 (GND), J1.B1 (GND), J1.B12 (GND), J1.SH (SHIELD), J3.1, R25.1, R27.1, R41.2, R99.2, R100.2, U4.7 (GND), U4.9 (EP), U8.1 (GND), U9.1 (GND); also elsewhere on the board
unnamed: C16.2, R28.1
unnamed: C38.1, D2.2 (A), U8.3 (VOUT)
unnamed: C39.1, D2.1 (K), D3.1 (K), U9.3 (VIN)
unnamed: C71.1, C72.2, Q1.4 (G), R40.2, SW1.2 (B)
unnamed: R41.1, SW1.1 (A)
unnamed: C14.2, U4.1 (BST)
unnamed: R28.2, U4.6 (COMP)
unnamed: R26.1, R27.2, U4.5 (FB)
unnamed: R25.2, U4.4 (RT/CLK)
unnamed: C14.1, L1.1, U4.8 (SW)
PACK+: C72.1, J3.2, Q1.1 (S), Q1.2 (S), Q1.3 (S), R40.1
USB_N: J1.A7 (D-), J1.B7 (D-); also elsewhere on the board
USB_P: J1.A6 (D+), J1.B6 (D+); also elsewhere on the board
VBUS: C37.1, J1.A4 (VBUS), J1.A9 (VBUS), J1.B4 (VBUS), J1.B9 (VBUS), U8.2 (VIN)
VCC: C5.1, C8.1, C12.1, D3.2 (A), L1.2, R26.2; also elsewhere on the board
VSYS: C15.2, C71.2, C73.2, C74.2, D4.1 (A1), Q1.5 (D), Q1.6 (D), Q1.7 (D), Q1.8 (D), U4.2 (VIN), U4.3 (EN); also elsewhere on the board

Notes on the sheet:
U8 makes 5 V from VBUS (up to 30 V in), so the MCU runs from USB alone: program it with no pack or the switch off. D2/D3 OR that with the buck's VCC. Keep U8's load to the MCU (~50 mA).
J3 takes the smart pack's XT30U-F lead (kicad-pack/goosepack): pin 1 GND = the pack's protected PACK-, pin 2 PACK+ (fused in the pack). Charging, protection and the 15 A fuse live in the pack. SW1 only drives Q1's gate; R40 holds Q1 off. Motor current flows through Q1 (AO4407A P-FET). With SW1 off 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
ERC FLAG
3.3 V RAIL (USB OR BATTERY)
USB-C: programming only (no charging). R99/R100 5.1k Rd on CC1/CC2 make it a plain 5 V sink. D+/D- continue on the MCU & USB sheet.
5 V BUCK (AP64500)
Vout = 0.8 V x (1 + R26/R27) = 4.96 V EN tied to VIN: always on R25 sets the switching frequency L1: Zeng Yi HMS0530-2R2M, 2.2 uH, Isat 9.0 A typ (30 % drop): above U4's 8 A typ limit, 0.2 A under its 9.2 A max; alloy powder, so it saturates softly. JLC places it. C73/C74: VIN bulk at U4's VIN pins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
USB-C (PROGRAMMING)
PACK INPUT + POWER SWITCH

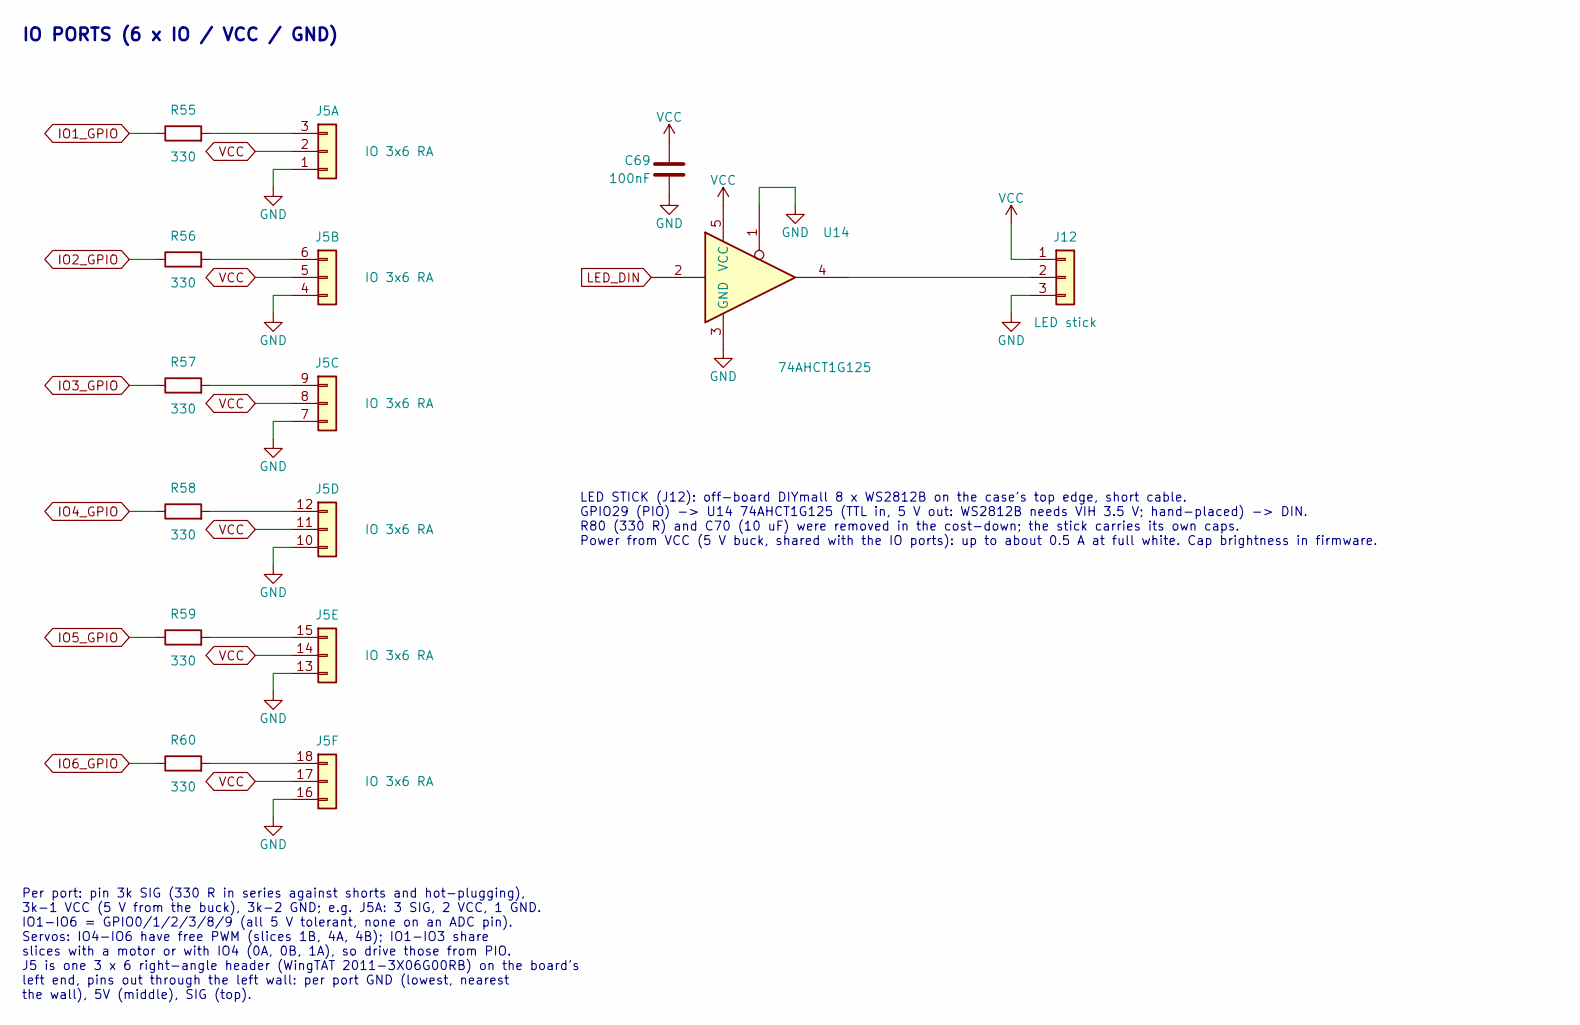
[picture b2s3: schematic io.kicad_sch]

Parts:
C69: 100nF; C_0402_1005Metric; MPN CL05B104KO5NNNC; LCSC Part # C1525
J5: IO 3x6 RA; PinHeader_3x06_P2.54mm_Horizontal_WingTAT; MPN 2011-3X06G00RB; LCSC Part # C51953246
J12: LED stick; JST_PH_B3B-PH-K_1x03_P2.00mm_Vertical; MPN B3B-PH-K-S(LF)(SN); LCSC Part # C131339
R55, R56, R57, R58, R59, R60: 330; R_0402_1005Metric; MPN 0402WGF3300TCE; LCSC Part # C25104
U14: 74AHCT1G125; SOT-23-5; MPN SN74AHCT1G125DBVR; LCSC Part # C20617903

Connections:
GND: C69.2, J5.1 (GND), J5.4 (GND), J5.7 (GND), J5.10 (GND), J5.13 (GND), J5.16 (GND), J12.3, U14.1, U14.3 (GND); also elsewhere on the board
IO1_GPIO: R55.1; also elsewhere on the board
IO2_GPIO: R56.1; also elsewhere on the board
IO3_GPIO: R57.1; also elsewhere on the board
IO4_GPIO: R58.1; also elsewhere on the board
IO5_GPIO: R59.1; also elsewhere on the board
IO6_GPIO: R60.1; also elsewhere on the board
LED_DIN: U14.2; also elsewhere on the board
unnamed: J5.3 (SIG), R55.2
unnamed: J5.6 (SIG), R56.2
unnamed: J5.9 (SIG), R57.2
unnamed: J5.12 (SIG), R58.2
unnamed: J5.15 (SIG), R59.2
unnamed: J5.18 (SIG), R60.2
unnamed: J12.2, U14.4
VCC: C69.1, J5.2 (5V), J5.5 (5V), J5.8 (5V), J5.11 (5V), J5.14 (5V), J5.17 (5V), J12.1, U14.5 (VCC); also elsewhere on the board

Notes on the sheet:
LED STICK (J12): off-board DIYmall 8 x WS2812B on the case's top edge, short cable. GPIO29 (PIO) -> U14 74AHCT1G125 (TTL in, 5 V out: WS2812B needs VIH 3.5 V; hand-placed) -> DIN. R80 (330 R) and C70 (10 uF) were removed in the cost-down; the stick carries its own caps. Power from VCC (5 V buck, sh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
Per port: pin 3k SIG (330 R in series against shorts and hot-plugging), 3k-1 VCC (5 V from the buck), 3k-2 GND; e.g. J5A: 3 SIG, 2 VCC, 1 GND. IO1-IO6 = GPIO0/1/2/3/8/9 (all 5 V tolerant, none on an ADC pin). Servos: IO4-IO6 have free PWM (slices 1B, 4A, 4B); IO1-IO3 share slices with a motor or wi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
IO PORTS (6 x IO / VCC / GND)
